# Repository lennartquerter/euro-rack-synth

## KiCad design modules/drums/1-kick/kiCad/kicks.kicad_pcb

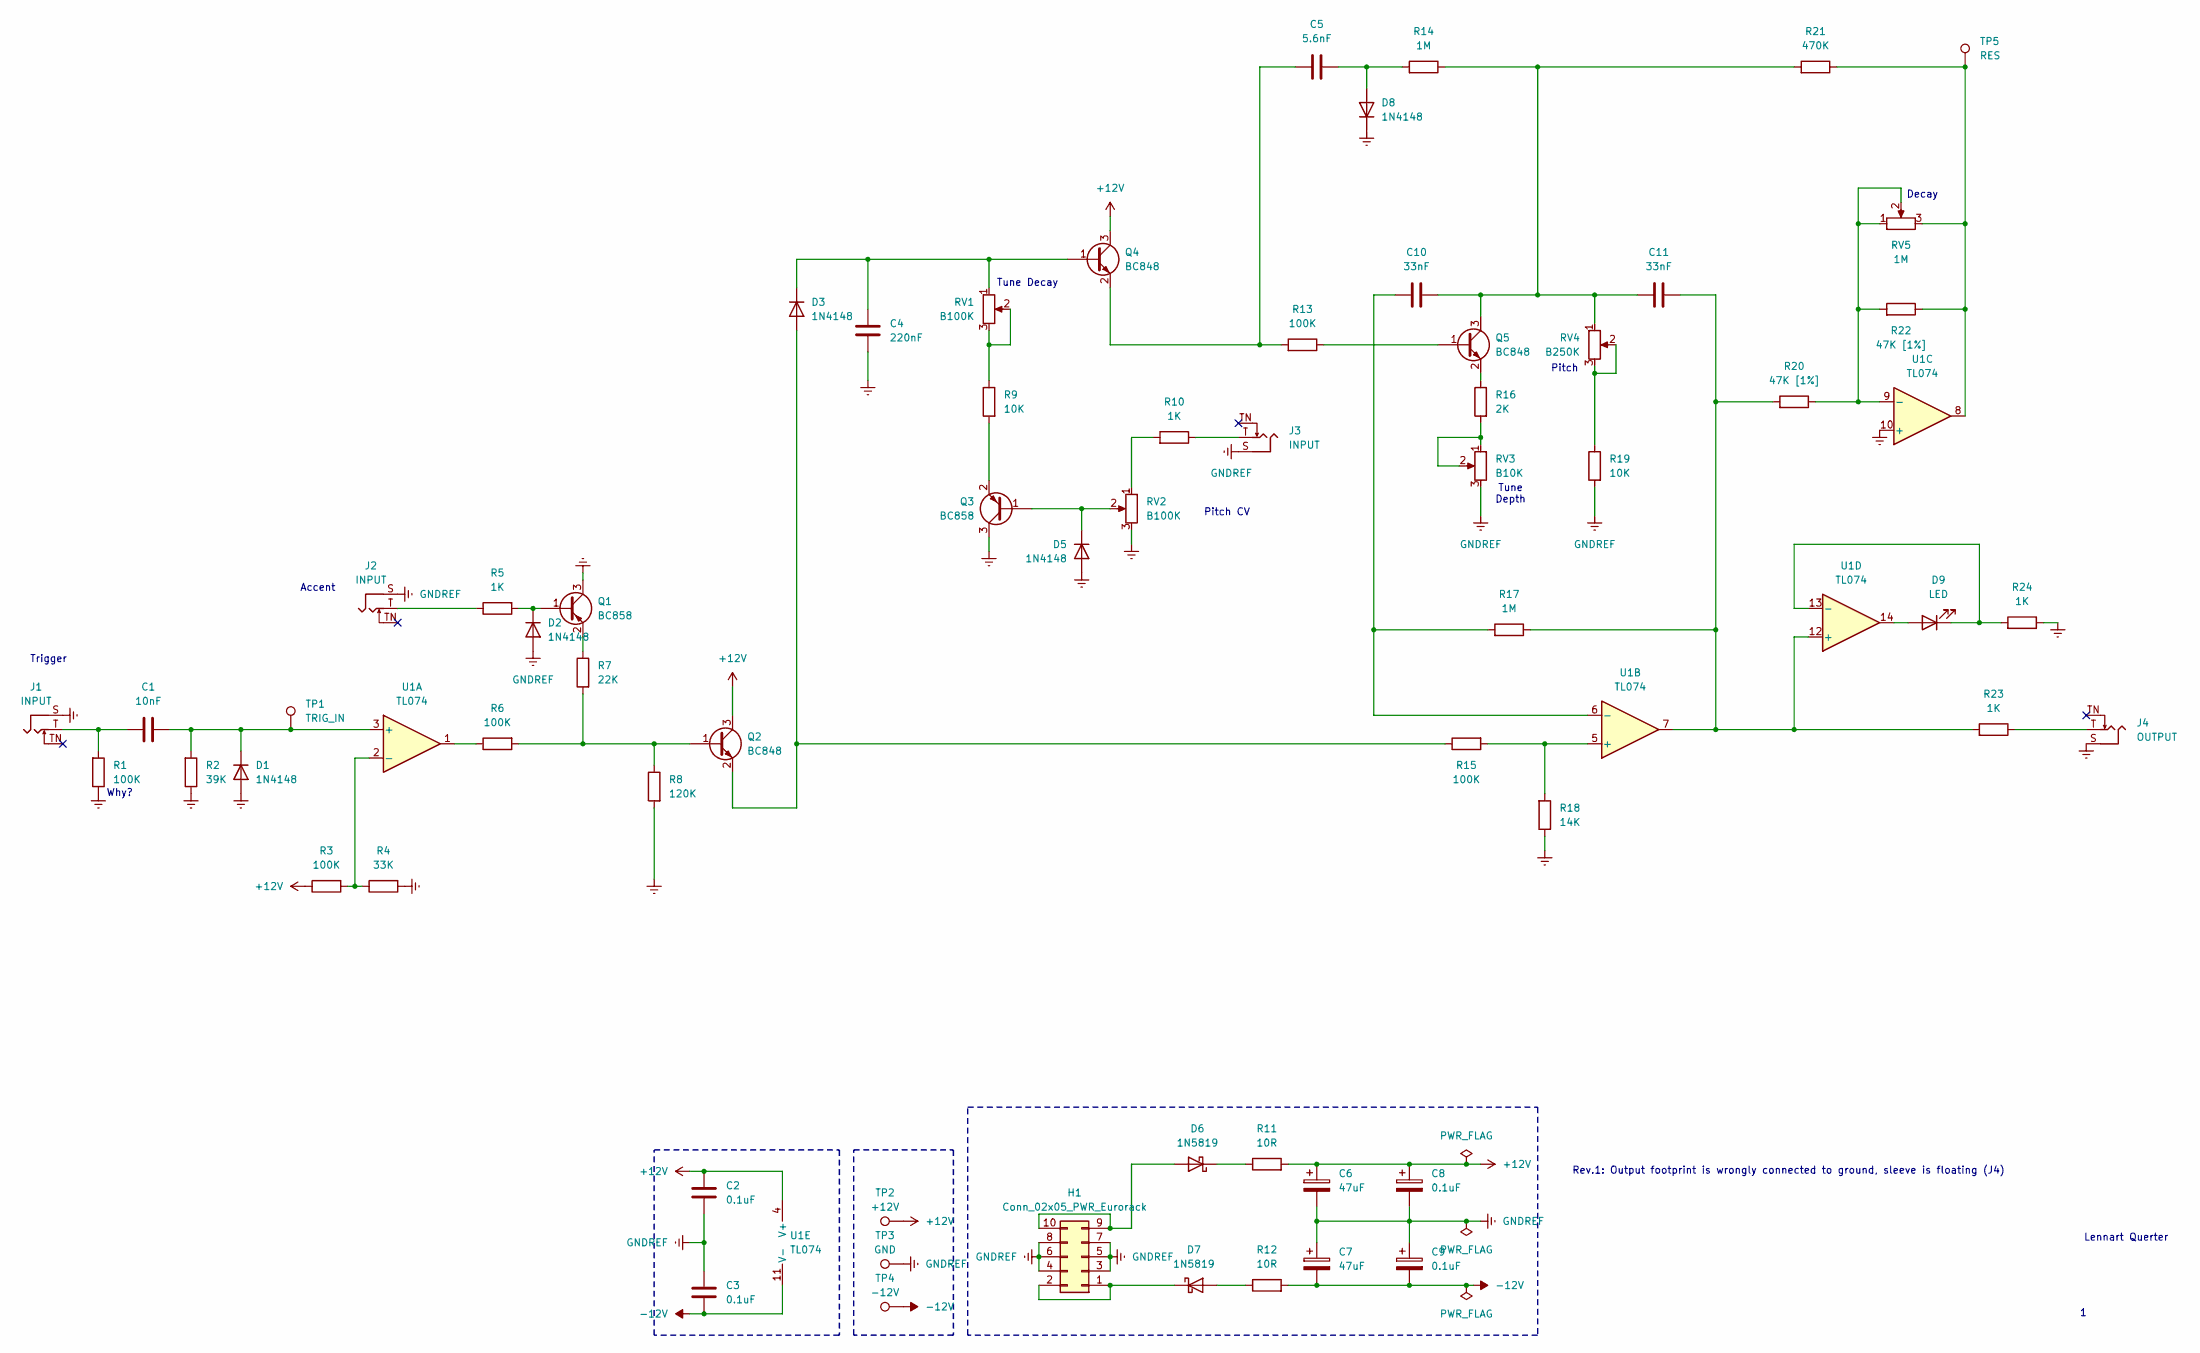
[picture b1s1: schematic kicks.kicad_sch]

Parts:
C1: 10nF; C_0805_2012Metric_Pad1.18x1.45mm_HandSolder
C2, C3: 0.1uF; C_0805_2012Metric_Pad1.18x1.45mm_HandSolder
C4: 220nF; C_0805_2012Metric_Pad1.18x1.45mm_HandSolder
C5: 5.6nF; C_0805_2012Metric_Pad1.18x1.45mm_HandSolder
C6, C7: 47uF; CP_Radial_D6.3mm_P2.50mm
C8, C9: 0.1uF; CP_Radial_D4.0mm_P2.00mm
C10, C11: 33nF; C_0805_2012Metric_Pad1.18x1.45mm_HandSolder
D1, D2, D3, D5, D8: 1N4148; D_SOD-323_HandSoldering
D6, D7: 1N5819; D_SOD-123
D9: LED; LED_D3.0mm
H1: Conn_02x05_PWR_Eurorack; IDC-Header_2x05_P2.54mm_Vertical
J1, J2, J3: INPUT; Jack_3.5mm_QingPu_WQP-PJ398SM_Vertical_CircularHoles
J4: OUTPUT; Jack_3.5mm_QingPu_WQP-PJ398SM_Vertical_CircularHoles
Q1, Q3: BC858; SOT-23
Q2, Q4, Q5: BC848; SOT-23
R1, R3, R6, R13, R15: 100K; R_0805_2012Metric_Pad1.20x1.40mm_HandSolder
R2: 39K; R_0805_2012Metric_Pad1.20x1.40mm_HandSolder
R4: 33K; R_0805_2012Metric_Pad1.20x1.40mm_HandSolder
R5, R10, R23, R24: 1K; R_0805_2012Metric_Pad1.20x1.40mm_HandSolder
R7: 22K; R_0805_2012Metric_Pad1.20x1.40mm_HandSolder
R8: 120K; R_0805_2012Metric_Pad1.20x1.40mm_HandSolder
R9, R19: 10K; R_0805_2012Metric_Pad1.20x1.40mm_HandSolder
R11, R12: 10R; R_0805_2012Metric_Pad1.20x1.40mm_HandSolder
R14, R17: 1M; R_0805_2012Metric_Pad1.20x1.40mm_HandSolder
R16: 2K; R_0805_2012Metric_Pad1.20x1.40mm_HandSolder
R18: 14K; R_0805_2012Metric_Pad1.20x1.40mm_HandSolder
R20, R22: 47K [1%]; R_0805_2012Metric_Pad1.20x1.40mm_HandSolder
R21: 470K; R_0805_2012Metric_Pad1.20x1.40mm_HandSolder
RV1, RV2: B100K; Potentiometer_TT_P0915N
RV3: B10K; Potentiometer_TT_P0915N
RV4: B250K; Potentiometer_TT_P0915N
RV5: 1M; Potentiometer_TT_P0915N
TP1: TRIG_IN; Pin_D1.0mm_L10.0mm
TP2: +12V; Pin_D1.0mm_L10.0mm
TP3: GND; Pin_D1.0mm_L10.0mm
TP4: -12V; Pin_D1.0mm_L10.0mm
TP5: RES; Pin_D1.0mm_L10.0mm
U1: TL074; SO-14_3.9x8.65mm_P1.27mm

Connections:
+12V: C2.1, C6.1, C8.1, Q2.3 (C), Q4.3 (C), R3.2, R11.2, TP2.1, U1.4 (V+)
-12V: C3.2, C7.2, C9.2, R12.2, TP4.1, U1.11 (V-)
GNDREF: C2.2, C3.1, C4.1, C6.2, C7.1, C8.2, C9.1, D1.2 (A), D2.2 (A), D5.2 (A), D8.1 (K), H1.3, H1.4, H1.5, H1.6, H1.7, H1.8, J1.S, J2.S, J3.S, J4.S, Q1.3 (C), Q3.3 (C), R1.2, R2.2, R4.1, R8.1, R18.2, R19.1, R24.2, RV2.3, RV3.3, TP3.1, U1.10 (+)
unnamed: C1.1, J1.T, R1.1
unnamed: C1.2, D1.1 (K), R2.1, TP1.1, U1.3 (+)
unnamed: D2.1 (K), Q1.1 (B), R5.1
unnamed: D3.2 (A), Q2.2 (E), R15.2
unnamed: C4.2, D3.1 (K), Q4.1 (B), RV1.1
unnamed: D5.1 (K), Q3.1 (B), RV2.2
unnamed: D6.2 (A), H1.9, H1.10
unnamed: D6.1 (K), R11.1
unnamed: D7.2 (A), R12.1
unnamed: D7.1 (K), H1.1, H1.2
unnamed: C5.2, D8.2 (A), R14.1
unnamed: D9.2 (A), U1.14
unnamed: D9.1 (K), R24.1, U1.13 (-)
unnamed: J2.T, R5.2
unnamed: J3.T, R10.2
unnamed: J4.T, R23.2
unnamed: Q1.2 (E), R7.2
unnamed: Q2.1 (B), R6.1, R7.1, R8.2
unnamed: Q3.2 (E), R9.1
unnamed: C5.1, Q4.2 (E), R13.1
unnamed: Q5.1 (B), R13.2
unnamed: C10.2, C11.1, Q5.3 (C), R14.2, R21.1, RV4.1
unnamed: Q5.2 (E), R16.2
unnamed: R6.2, U1.1
unnamed: R9.2, RV1.2, RV1.3
unnamed: R10.1, RV2.1
unnamed: R16.1, RV3.1, RV3.2
unnamed: R19.2, RV4.2, RV4.3
unnamed: R21.2, R22.2, RV5.3, TP5.1, U1.8
unnamed: R3.1, R4.2, U1.2 (-)
unnamed: R15.1, R18.1, U1.5 (+)
unnamed: C10.1, R17.1, U1.6 (-)
unnamed: R20.2, R22.1, RV5.1, RV5.2, U1.9 (-)
unnamed: C11.2, R17.2, R20.1, R23.1, U1.7, U1.12 (+)

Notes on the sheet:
Rev.1: Output footprint is wrongly connected to ground, sleeve is floating (J4)
Trigger
Pitch
Decay
Tune Depth
Why?
Tune Decay
Accent
Lennart Querter
Pitch CV

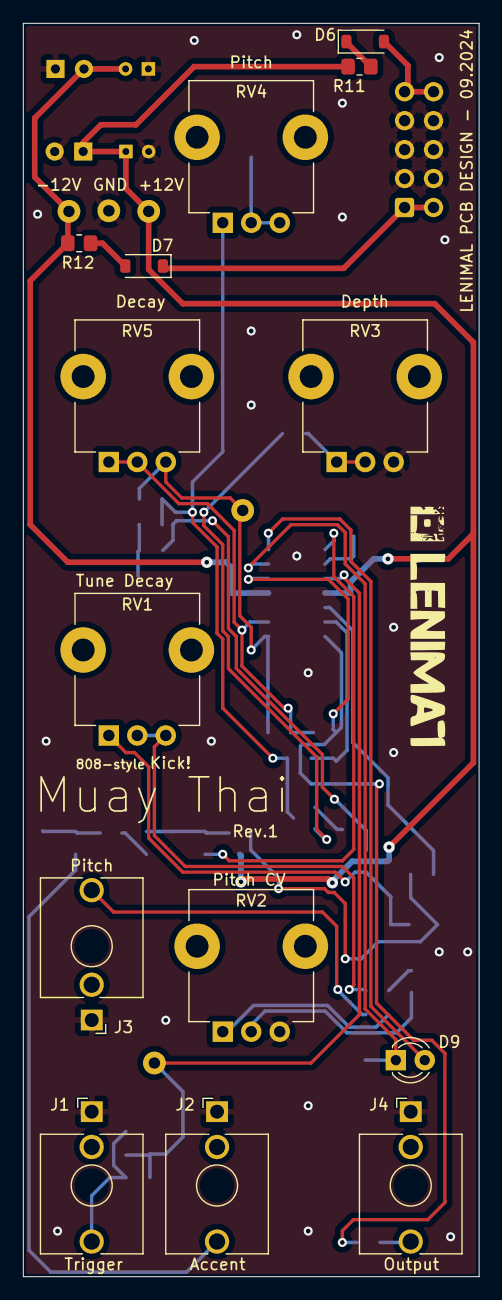
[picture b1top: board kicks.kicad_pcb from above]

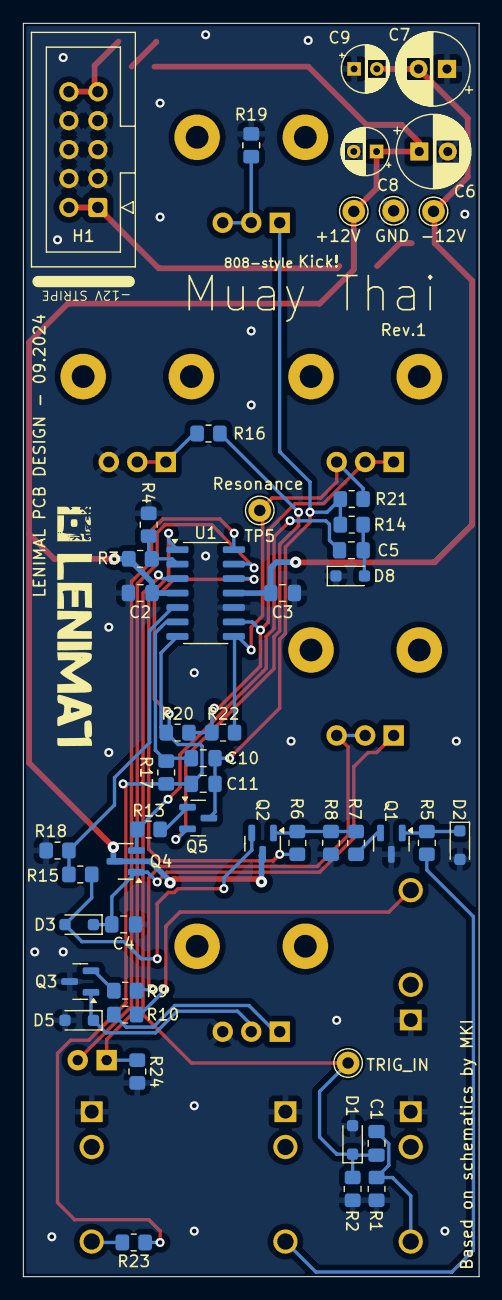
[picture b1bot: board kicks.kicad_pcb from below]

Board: 2 copper layers, 40.0 x 110.0 mm, 64 parts (50 on the bottom side), 37 nets.

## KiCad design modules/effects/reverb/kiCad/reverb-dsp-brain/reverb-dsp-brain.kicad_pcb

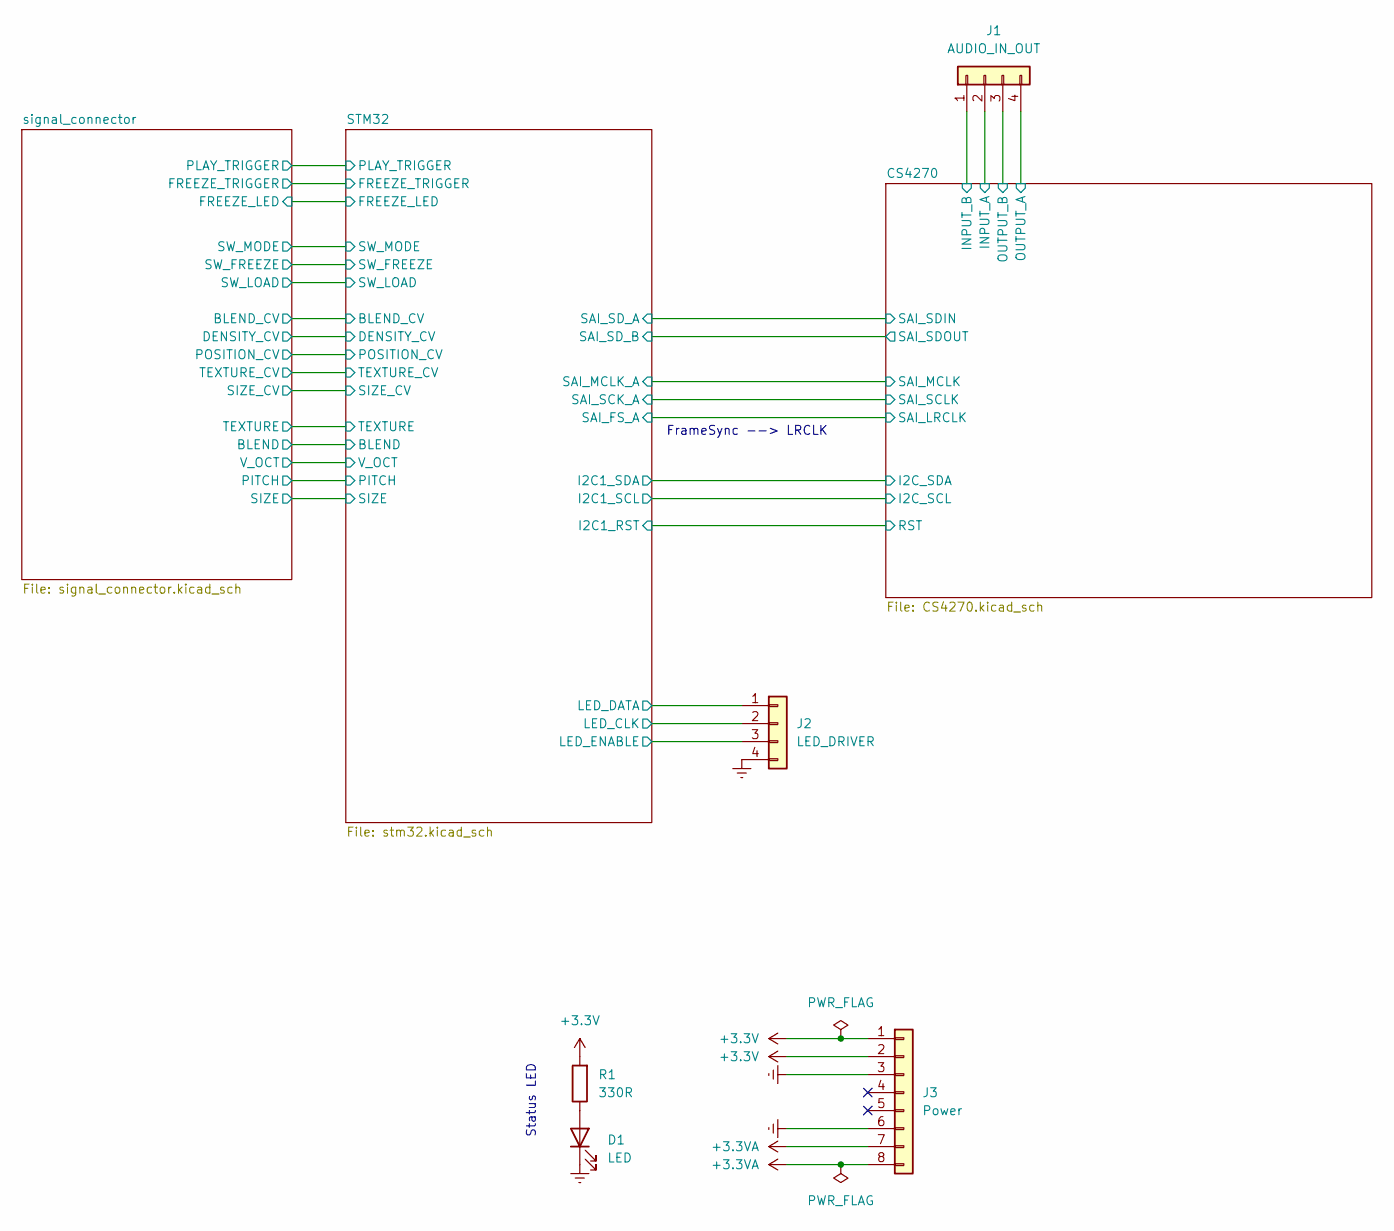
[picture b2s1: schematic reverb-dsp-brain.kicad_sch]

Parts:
D1: LED; LED_0805_2012Metric_Pad1.15x1.40mm_HandSolder
J1: AUDIO_IN_OUT; PinHeader_1x04_P2.54mm_Vertical
J2: LED_DRIVER; PinHeader_1x04_P2.54mm_Vertical
J3: Power; PinHeader_1x08_P2.54mm_Vertical
R1: 330R; R_0805_2012Metric_Pad1.20x1.40mm_HandSolder

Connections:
+3.3V: J3.1, J3.2, R1.2; also elsewhere on the board
+3.3VA: J3.7, J3.8; also elsewhere on the board
/CS4270/INPUT_A: J1.2; also elsewhere on the board
/CS4270/INPUT_B: J1.1; also elsewhere on the board
/CS4270/OUTPUT_A: J1.4; also elsewhere on the board
/CS4270/OUTPUT_B: J1.3; also elsewhere on the board
/STM32/LED_CLK: J2.2; also elsewhere on the board
/STM32/LED_DATA: J2.1; also elsewhere on the board
/STM32/LED_ENABLE: J2.3; also elsewhere on the board
GNDREF: D1.1 (K), J2.4, J3.3, J3.6; also elsewhere on the board
unnamed: D1.2 (A), R1.1

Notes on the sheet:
FrameSync --> LRCLK
Status LED

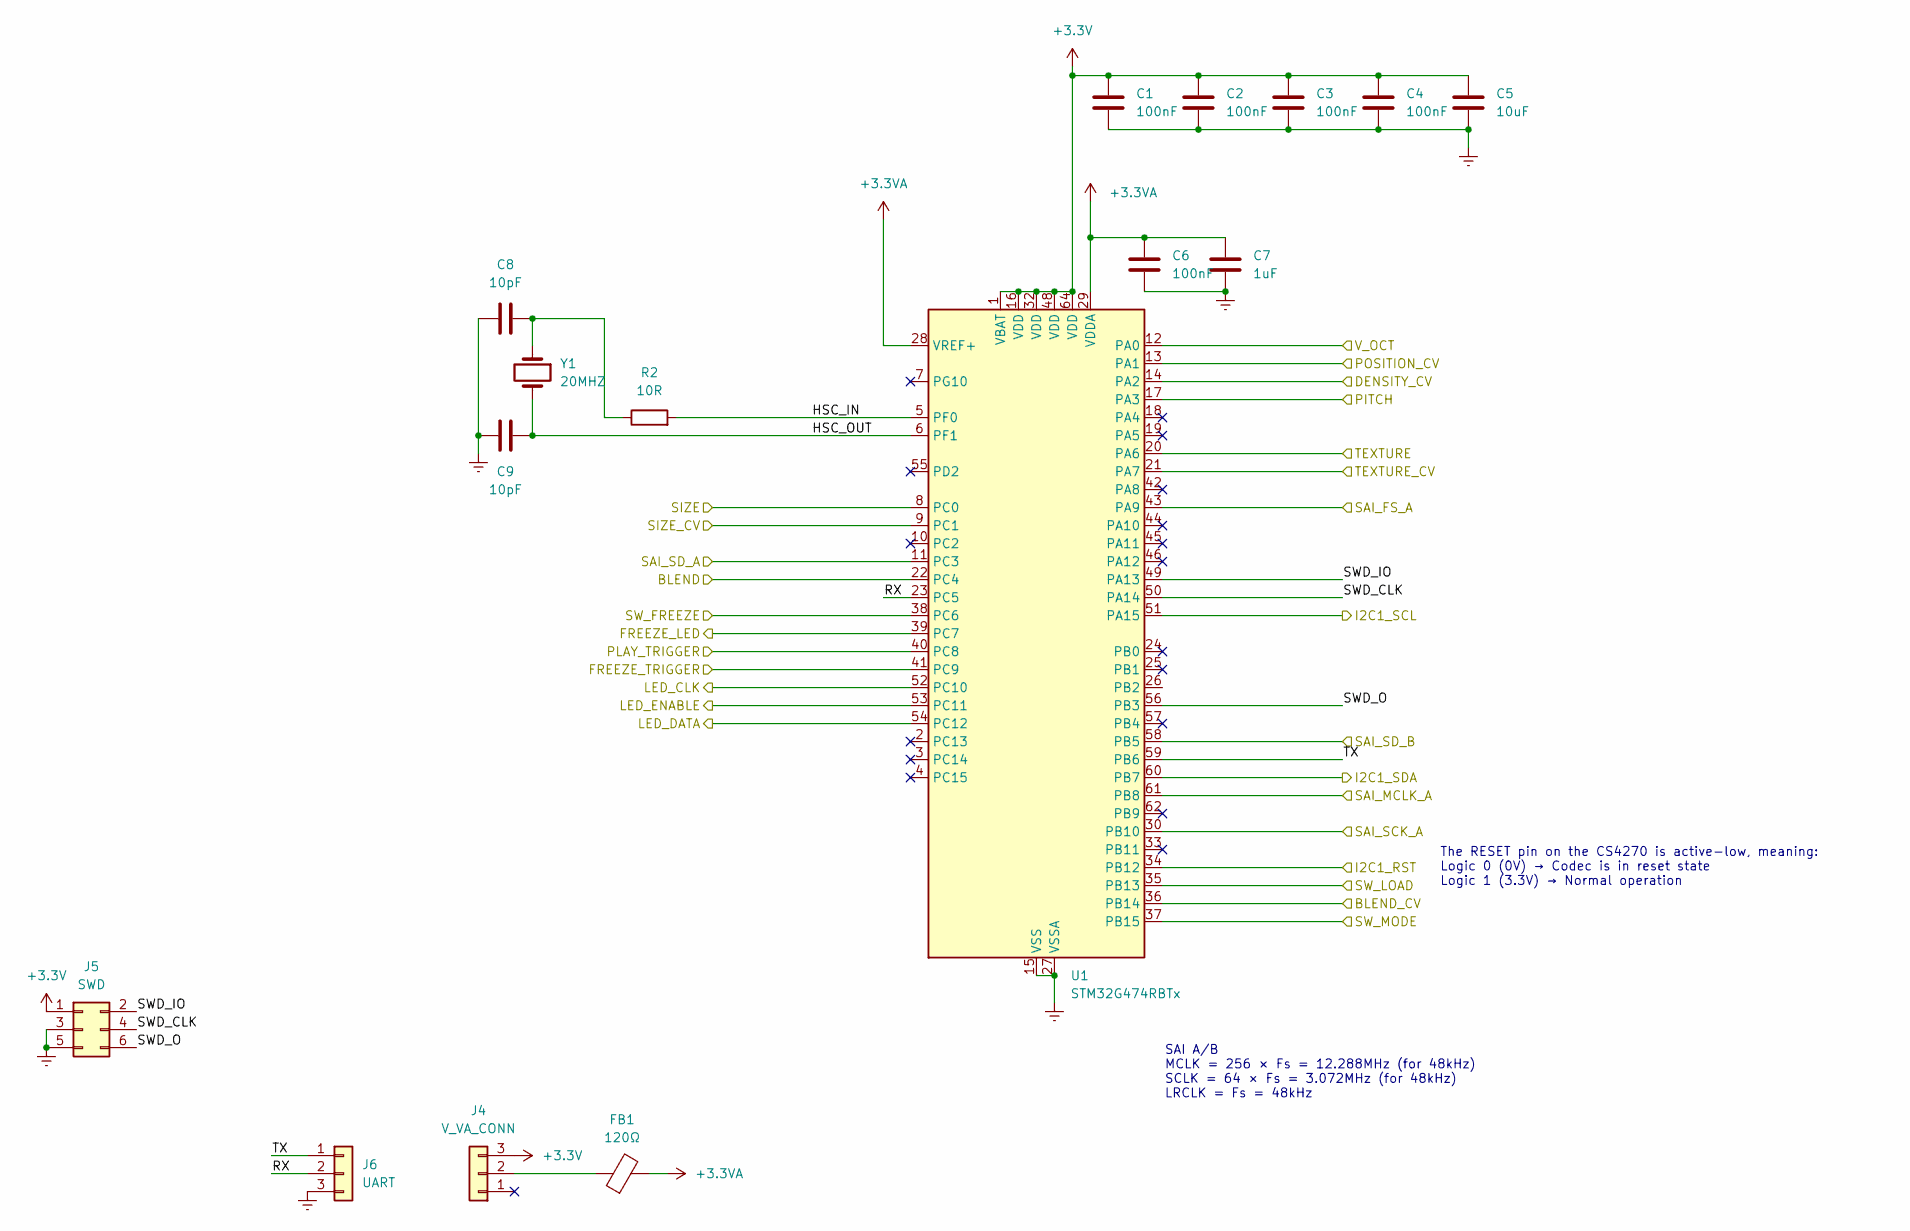
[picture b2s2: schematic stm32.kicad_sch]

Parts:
C1, C2, C3, C4, C6: 100nF; C_0805_2012Metric_Pad1.18x1.45mm_HandSolder
C5: 10uF; C_0805_2012Metric_Pad1.18x1.45mm_HandSolder
C7: 1uF; C_0805_2012Metric_Pad1.18x1.45mm_HandSolder
C8, C9: 10pF; C_0805_2012Metric_Pad1.18x1.45mm_HandSolder
FB1: 120Ω; L_0805_2012Metric_Pad1.15x1.40mm_HandSolder
J4: V_VA_CONN; PinHeader_1x03_P2.54mm_Vertical
J5: SWD; PinHeader_2x03_P2.54mm_Vertical
J6: UART; PinHeader_1x03_P2.54mm_Vertical
R2: 10R; R_0805_2012Metric_Pad1.20x1.40mm_HandSolder
U1: STM32G474RBTx; LQFP-64_10x10mm_P0.5mm
Y1: 20MHZ; Crystal_SMD_HC49-SD_HandSoldering

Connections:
+3.3V: C1.2, C2.2, C3.2, C4.2, C5.2, J4.3, J5.1, U1.1 (VBAT), U1.16 (VDD), U1.32 (VDD), U1.48 (VDD), U1.64 (VDD); also elsewhere on the board
+3.3VA: C6.2, C7.2, FB1.2, U1.28 (VREF+), U1.29 (VDDA); also elsewhere on the board
/CS4270/I2C_SCL: U1.51 (PA15); also elsewhere on the board
/CS4270/I2C_SDA: U1.60 (PB7); also elsewhere on the board
/CS4270/RST: U1.34 (PB12); also elsewhere on the board
/CS4270/SAI_LRCLK: U1.43 (PA9); also elsewhere on the board
/CS4270/SAI_MCLK: U1.61 (PB8); also elsewhere on the board
/CS4270/SAI_SCLK: U1.33 (PB11); also elsewhere on the board
/CS4270/SAI_SDIN: U1.11 (PC3); also elsewhere on the board
/CS4270/SAI_SDOUT: U1.58 (PB5); also elsewhere on the board
/STM32/BLEND: U1.22 (PC4); also elsewhere on the board
/STM32/BLEND_CV: U1.36 (PB14); also elsewhere on the board
/STM32/DENSITY_CV: U1.14 (PA2); also elsewhere on the board
/STM32/FREEZE_LED: U1.39 (PC7); also elsewhere on the board
/STM32/FREEZE_TRIGGER: U1.41 (PC9); also elsewhere on the board
/STM32/HSC_IN: R2.2, U1.5 (PF0)
/STM32/HSC_OUT: C9.1, U1.6 (PF1), Y1.2
/STM32/LED_CLK: U1.52 (PC10); also elsewhere on the board
/STM32/LED_DATA: U1.54 (PC12); also elsewhere on the board
/STM32/LED_ENABLE: U1.53 (PC11); also elsewhere on the board
/STM32/PITCH: U1.17 (PA3); also elsewhere on the board
/STM32/PLAY_TRIGGER: U1.40 (PC8); also elsewhere on the board
/STM32/POSITION_CV: U1.13 (PA1); also elsewhere on the board
/STM32/RX: J6.2, U1.23 (PC5)
/STM32/SIZE: U1.8 (PC0); also elsewhere on the board
/STM32/SIZE_CV: U1.9 (PC1); also elsewhere on the board
/STM32/SWD_CLK: J5.4, U1.50 (PA14)
/STM32/SWD_IO: J5.2, U1.49 (PA13)
/STM32/SWD_O: J5.6, U1.56 (PB3)
/STM32/SW_FREEZE: U1.38 (PC6); also elsewhere on the board
/STM32/SW_LOAD: U1.35 (PB13); also elsewhere on the board
/STM32/SW_MODE: U1.37 (PB15); also elsewhere on the board
/STM32/TEXTURE: U1.20 (PA6); also elsewhere on the board
/STM32/TEXTURE_CV: U1.21 (PA7); also elsewhere on the board
/STM32/TX: J6.1, U1.59 (PB6)
/STM32/V_OCT: U1.12 (PA0); also elsewhere on the board
GNDREF: C1.1, C2.1, C3.1, C4.1, C5.1, C6.1, C7.1, C8.2, C9.2, J5.3, J5.5, J6.3, U1.15 (VSS), U1.27 (VSSA), U1.31 (VSS), U1.47 (VSS), U1.63 (VSS); also elsewhere on the board
unnamed: C8.1, R2.1, Y1.1
unnamed: FB1.1, J4.2

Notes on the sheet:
SAI A/B MCLK = 256 × Fs = 12.288MHz (for 48kHz) SCLK = 64 × Fs = 3.072MHz (for 48kHz) LRCLK = Fs = 48kHz
The RESET pin on the CS4270 is active-low, meaning: Logic 0 (0V) → Codec is in reset state Logic 1 (3.3V) → Normal operation

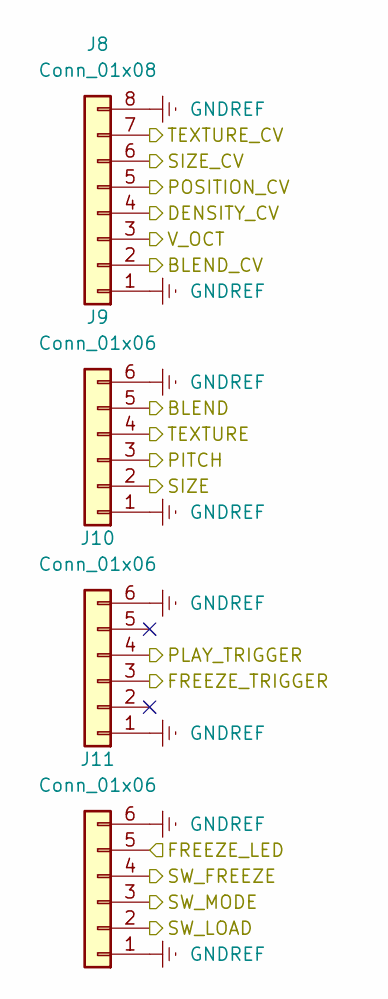
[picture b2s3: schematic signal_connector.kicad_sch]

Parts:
J8: Conn_01x08; PinHeader_1x08_P2.54mm_Vertical
J9, J10, J11: Conn_01x06; PinHeader_1x06_P2.54mm_Vertical

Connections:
/STM32/BLEND: J9.5; also elsewhere on the board
/STM32/BLEND_CV: J8.2; also elsewhere on the board
/STM32/DENSITY_CV: J8.4; also elsewhere on the board
/STM32/FREEZE_LED: J11.5; also elsewhere on the board
/STM32/FREEZE_TRIGGER: J10.3; also elsewhere on the board
/STM32/PITCH: J9.3; also elsewhere on the board
/STM32/PLAY_TRIGGER: J10.4; also elsewhere on the board
/STM32/POSITION_CV: J8.5; also elsewhere on the board
/STM32/SIZE: J9.2; also elsewhere on the board
/STM32/SIZE_CV: J8.6; also elsewhere on the board
/STM32/SW_FREEZE: J11.4; also elsewhere on the board
/STM32/SW_LOAD: J11.2; also elsewhere on the board
/STM32/SW_MODE: J11.3; also elsewhere on the board
/STM32/TEXTURE: J9.4; also elsewhere on the board
/STM32/TEXTURE_CV: J8.7; also elsewhere on the board
/STM32/V_OCT: J8.3; also elsewhere on the board
GNDREF: J8.1, J8.8, J9.1, J9.6, J10.1, J10.6, J11.1, J11.6; also elsewhere on the board

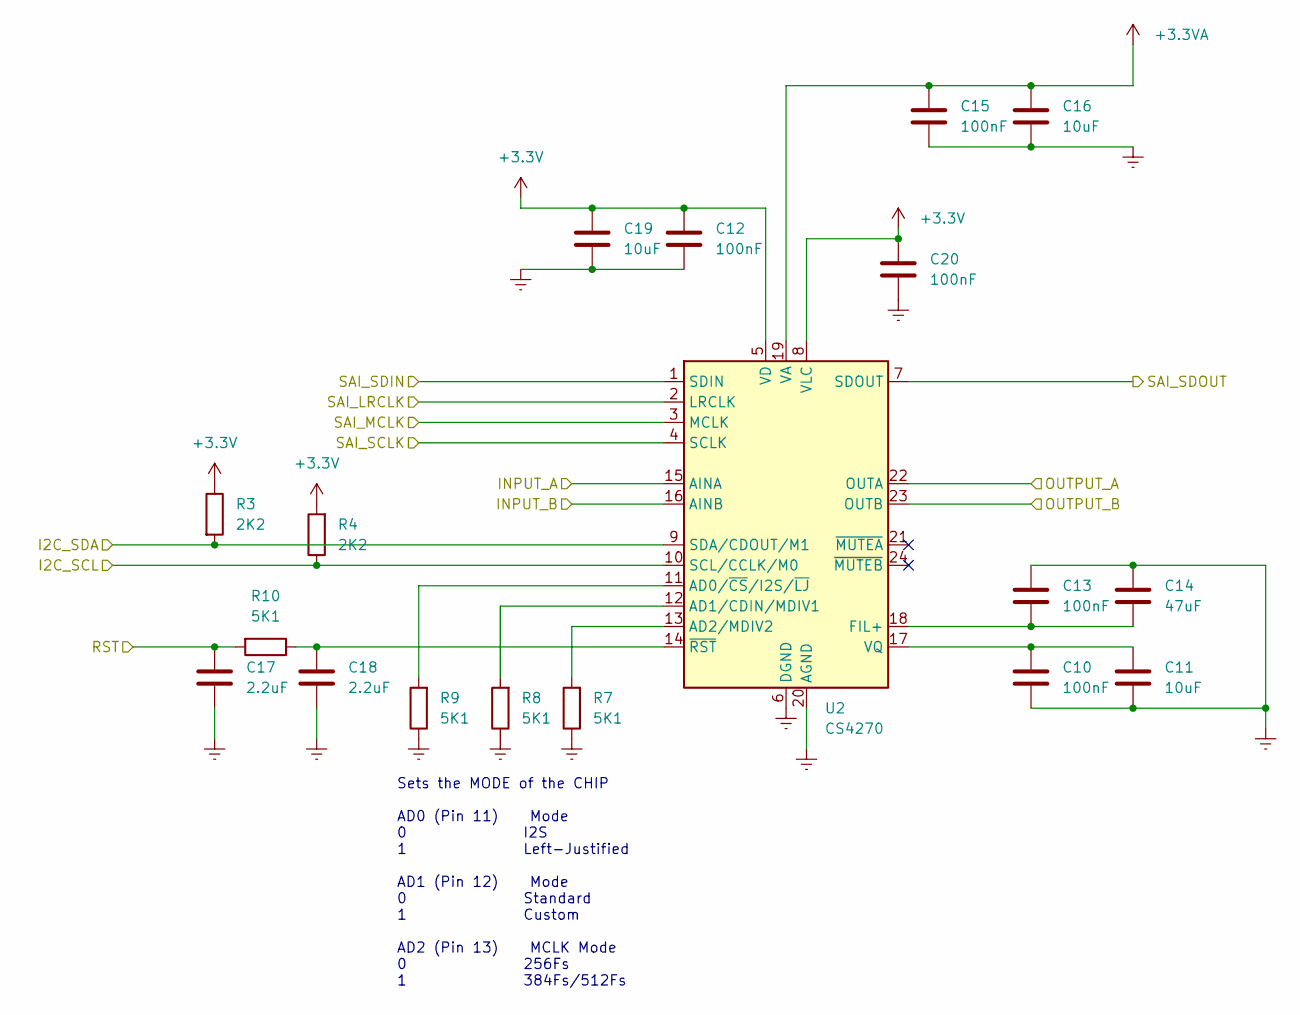
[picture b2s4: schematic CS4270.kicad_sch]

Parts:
C10, C12, C13, C15, C20: 100nF; C_0805_2012Metric_Pad1.18x1.45mm_HandSolder
C11, C16, C19: 10uF; C_0805_2012Metric_Pad1.18x1.45mm_HandSolder
C14: 47uF; C_0805_2012Metric_Pad1.18x1.45mm_HandSolder
C17, C18: 2.2uF; C_0805_2012Metric_Pad1.18x1.45mm_HandSolder
R3, R4: 2K2; R_0805_2012Metric_Pad1.20x1.40mm_HandSolder
R7, R8, R9, R10: 5K1; R_0805_2012Metric_Pad1.20x1.40mm_HandSolder
U2: CS4270; TSSOP-24_4.4x7.8mm_P0.65mm

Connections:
+3.3V: C12.1, C19.1, C20.1, R3.1, R4.2, U2.5 (VD), U2.8 (VLC); also elsewhere on the board
+3.3VA: C15.1, C16.1, U2.19 (VA); also elsewhere on the board
/CS4270/I2C_SCL: R4.1, U2.10 (SCL/CCLK/M0); also elsewhere on the board
/CS4270/I2C_SDA: R3.2, U2.9 (SDA/CDOUT/M1); also elsewhere on the board
/CS4270/INPUT_A: U2.15 (AINA); also elsewhere on the board
/CS4270/INPUT_B: U2.16 (AINB); also elsewhere on the board
/CS4270/OUTPUT_A: U2.22 (OUTA); also elsewhere on the board
/CS4270/OUTPUT_B: U2.23 (OUTB); also elsewhere on the board
/CS4270/RST: C17.1, R10.2; also elsewhere on the board
/CS4270/SAI_LRCLK: U2.2 (LRCLK); also elsewhere on the board
/CS4270/SAI_MCLK: U2.3 (MCLK); also elsewhere on the board
/CS4270/SAI_SCLK: U2.4 (SCLK); also elsewhere on the board
/CS4270/SAI_SDIN: U2.1 (SDIN); also elsewhere on the board
/CS4270/SAI_SDOUT: U2.7 (SDOUT); also elsewhere on the board
GNDREF: C10.2, C11.2, C12.2, C13.1, C14.1, C15.2, C16.2, C17.2, C18.2, C19.2, C20.2, R7.1, R8.1, R9.1, U2.6 (DGND), U2.20 (AGND); also elsewhere on the board
unnamed: R9.2, U2.11 (AD0/~CS/I2S/~LJ)
unnamed: R8.2, U2.12 (AD1/CDIN/MDIV1)
unnamed: R7.2, U2.13 (AD2/MDIV2)
unnamed: C13.2, C14.2, U2.18 (FIL+)
unnamed: C10.1, C11.1, U2.17 (VQ)
unnamed: C18.1, R10.1, U2.14 (~RST)

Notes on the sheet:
Sets the MODE of the CHIP AD0 (Pin 11) Mode 0 I2S 1 Left-Justified AD1 (Pin 12) Mode 0 Standard 1 Custom AD2 (Pin 13) MCLK Mode 0 256Fs 1 384Fs/512Fs

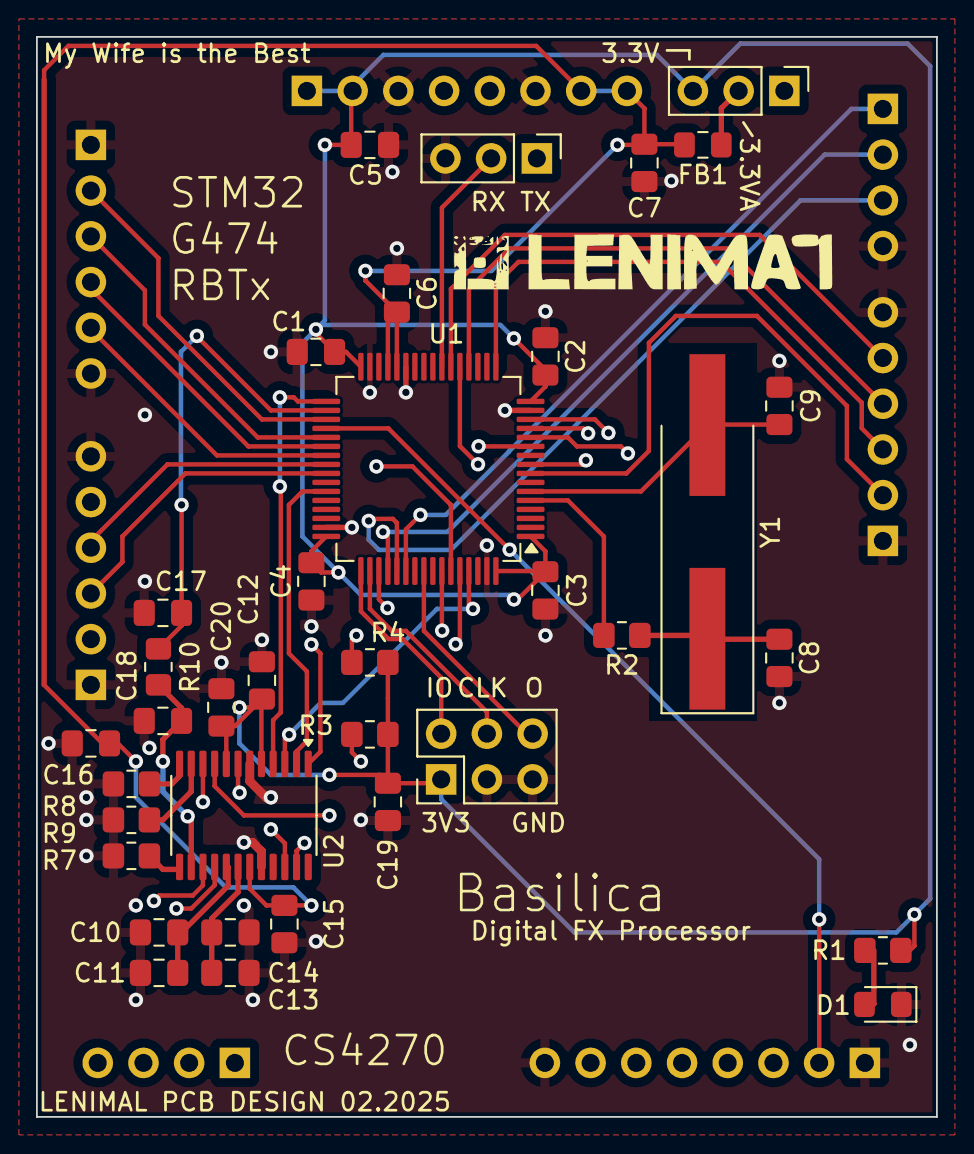
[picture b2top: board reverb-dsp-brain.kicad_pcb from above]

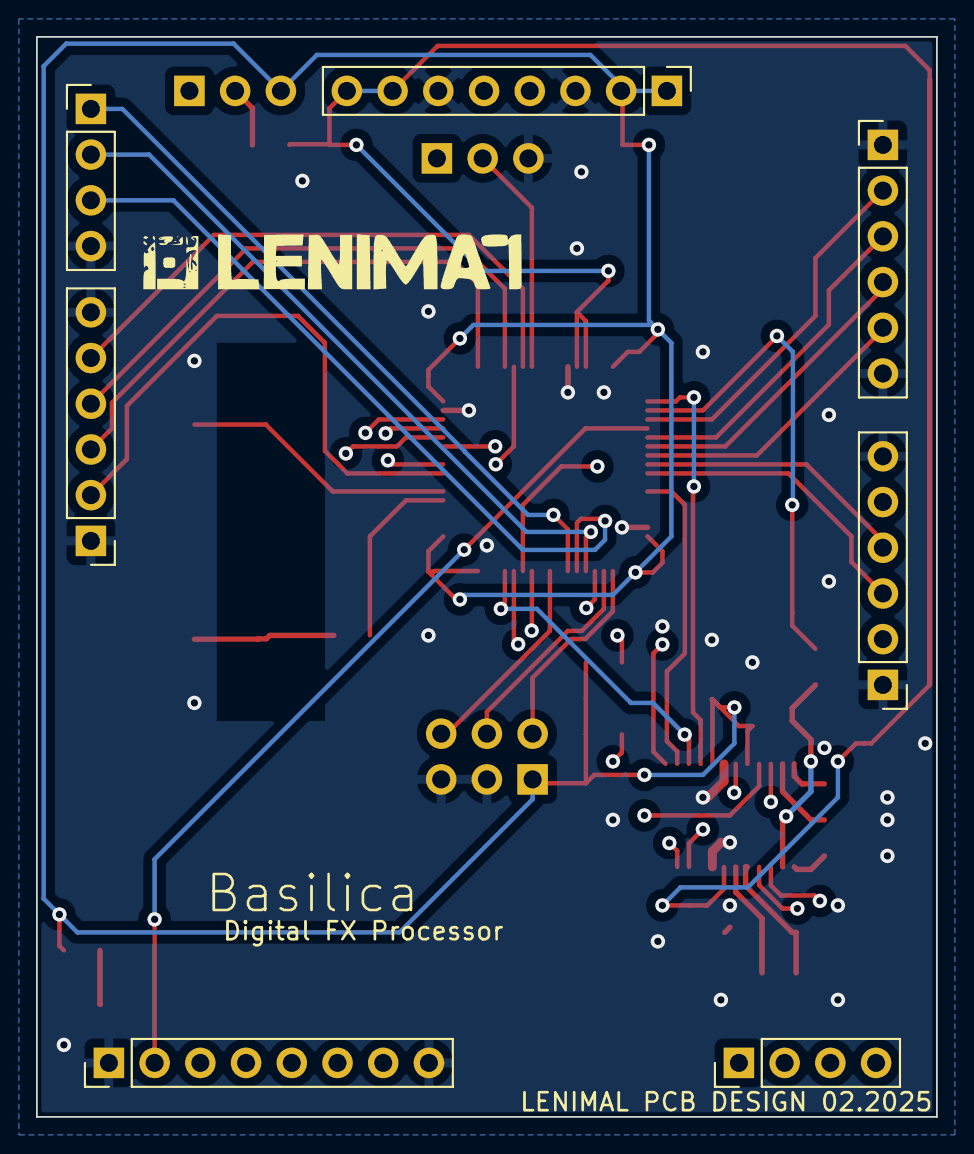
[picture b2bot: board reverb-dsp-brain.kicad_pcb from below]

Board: 4 copper layers, 50.0 x 60.0 mm, 43 parts (7 on the bottom side), 50 nets.
